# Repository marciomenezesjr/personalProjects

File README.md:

# Personal Projects - Marcio Menezes
This repository has been created with the intention to share some personal projects which I have been developing lately. In time I intend to share projects developed in the past, however it will take some time to clean up and document older projects so they can be shared.

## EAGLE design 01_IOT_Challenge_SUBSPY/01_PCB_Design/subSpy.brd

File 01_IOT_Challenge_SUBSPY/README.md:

# **Internet of Things Challenge**

* Marcio Jose de Menezes

[//]: # (Image References)

[image1]: 06_Images/InternetOfThings.jpg "IoT Challenge Award"

## **1. Introduction: The SubSpy Project**
This project has been developed for the Internet of Things (IoT) contest and has been awarded the first place on the competition. The project has been dubbed SubSpy, since it is a device to capture network packets (spy) in a sub-GHz (sub) wireless sensor network.

 The competition goal was to design a USB wireless adapter to enable handheld devices to connect to an existing sub-GHz underground wireless sensor network used in a project which targets the monitoring of soil moisture in a reforestation project in Cameroon, but could also serve any other underground monitoring application.

Besides the construction of the wireless adapter, a graphical user interface (GUI) was also required, in order to log the sensor's data as well as graphically plot the sensor's readings. The following criteria ([IoT_Project_Evaluation.pdf](08_References/IoT_Project_Evaluation.pdf)) have been used to evaluate the projects:
* Implementation with least number of components
* Low power consumption
* Successful data reception and visualization
* User friendly graphical interface (voted by all students and professors)
* Cost effective solution

The SubSpy project has excelled in each of the evaluating points, being awarded the first place on the challenge.

![alt text][image1]
Image 1: IoT Challenge award

## **2. Content**
Below, the work developed along this project is listed, for further information, refer to the final project report [finalReportIOT.pdf](07_Final_Report/finalReportIOT_lowResolution.pdf)

* Hardware design of the wireless adapter using EAGLE
* Prototype assembly
* Arduino RFM69CW library ported to Texas Instruments MSP430F5529
* Wireless adapter (SubSpy) firmware development in C programming language
* Graphical User Interface developed in cpp using QT framework
* Power consumption profiling benchmarks using EnergyTrace

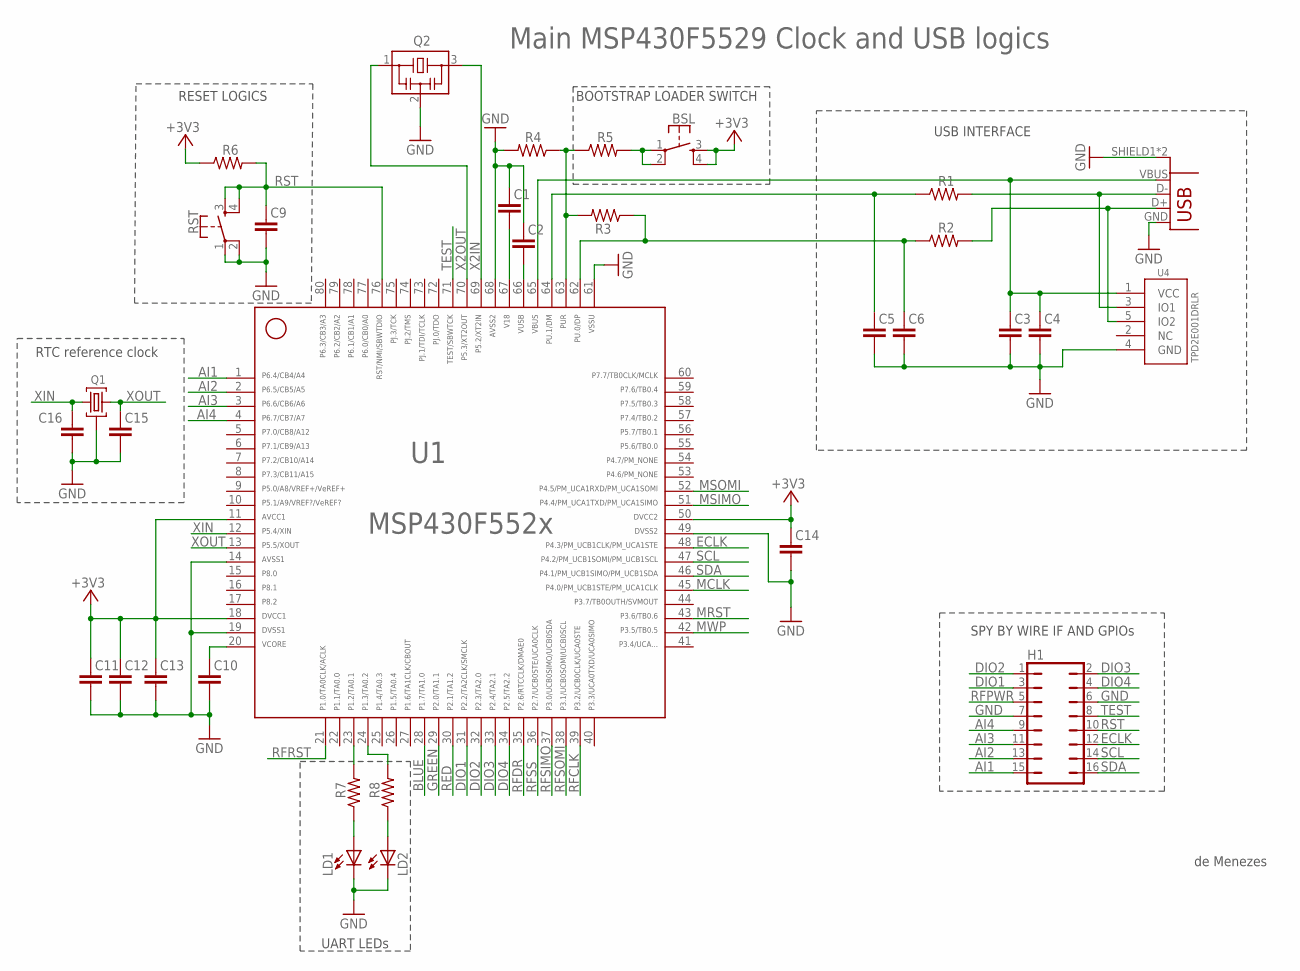
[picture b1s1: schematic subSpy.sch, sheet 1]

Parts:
BSL: DTSM-6
C1, C2: 220nF; C0402
C3: 10uF; C1206
C4, C12, C13, C14: 100nF; C0402
C5, C6: 10pF; C0603
C9: 1nF; C0603
C10: 470nF; C0603
C11: 10uF; C0805
C15, C16: 12pF; C0603
H1: JP8Q
LD1, LD2: LEDCHIP-LED0805; CHIP-LED0805
Q1: 32.768kHz; MS3V-T1R
Q2: CSTCR4M00G15L99; MURATA-FILTER_CSTCR
R1, R2: 27R; R0603
R3: 1.4k; R0603
R4: 1M; R0603
R5: 100R; R0603
R6: 47k; R0603
R7: 470R; R0603
R8: 390R; R0603
RST: DTSM-6
U1: MSP430F5529IPNR; PN80
U4: TPD2E001DRLR; TPD2E001-DRL
USB: USB_SMD; USBCONN

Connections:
+3V3: BSL.3, BSL.4, C11.1, C12.1, C13.1, C14.1, R6.1, U1.11, U1.18, U1.50; also elsewhere on the board
AI1: H1.15, U1.1
AI2: H1.13, U1.2
AI3: H1.11, U1.3
AI4: H1.9, U1.4
BLUE: U1.28; also elsewhere on the board
D+: R2.2, U4.5 (IO2), USB.D+
D-: R1.2, U4.3 (IO1), USB.D-
DIO1: H1.3, U1.31
DIO2: H1.1, U1.32
DIO3: H1.2, U1.33
DIO4: H1.4, U1.34
DM: C5.1, R1.1, U1.64
DP: C6.1, R2.1, R3.1, U1.62
ECLK: H1.12, U1.48
GND: C1.1, C2.1, C3.2, C4.2, C5.2, C6.2, C9.2, C10.2, C11.2, C12.2, C13.2, C14.2, C15.2, C16.2, H1.6, H1.7, LD1.C, LD2.C, Q1.P3 (GND), Q2.2, R4.2, RST.1, RST.2, U1.14, U1.19, U1.49, U1.61, U1.68, U4.4 (GND), USB.GND, USB.SHIELD1 (SHIELD), USB.SHIELD2 (SHIELD); also elsewhere on the board
GREEN: U1.29; also elsewhere on the board
LD1: R7.2, U1.23
LD2: R8.2, U1.24
MCLK: U1.45; also elsewhere on the board
MRST: U1.43; also elsewhere on the board
MSIMO: U1.51; also elsewhere on the board
MSOMI: U1.52; also elsewhere on the board
MWP: U1.42; also elsewhere on the board
unnamed: BSL.1, BSL.2, R5.2
unnamed: C10.1, U1.20
unnamed: LD1.A, R7.1
unnamed: LD2.A, R8.1
PUR: R3.2, R4.1, R5.1, U1.63
RED: U1.30; also elsewhere on the board
RFCLK: U1.39; also elsewhere on the board
RFDR: U1.35; also elsewhere on the board
RFPWR: H1.5; also elsewhere on the board
RFRST: U1.21; also elsewhere on the board
RFSIMO: U1.37; also elsewhere on the board
RFSOMI: U1.38; also elsewhere on the board
RFSS: U1.36; also elsewhere on the board
RST: C9.1, H1.10, R6.2, RST.3, RST.4, U1.76
SCL: H1.14, U1.47
SDA: H1.16, U1.46
TEST: H1.8, U1.71
V18: C1.2, U1.67
VBUS: C3.1, C4.1, U1.65, U4.1 (VCC), USB.VBUS; also elsewhere on the board
VUSB: C2.2, U1.66
X2IN: Q2.3, U1.69
X2OUT: Q2.1, U1.70
XIN: C16.1, Q1.P2 (2), U1.12
XOUT: C15.1, Q1.P1 (1), U1.13

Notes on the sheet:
UART LEDs
SPY BY WIRE IF AND GPIOs
USB INTERFACE
BOOTSTRAP LOADER SWITCH
RESET LOGICS
Main MSP430F5529 Clock and USB logics
RTC reference clock
de Menezes

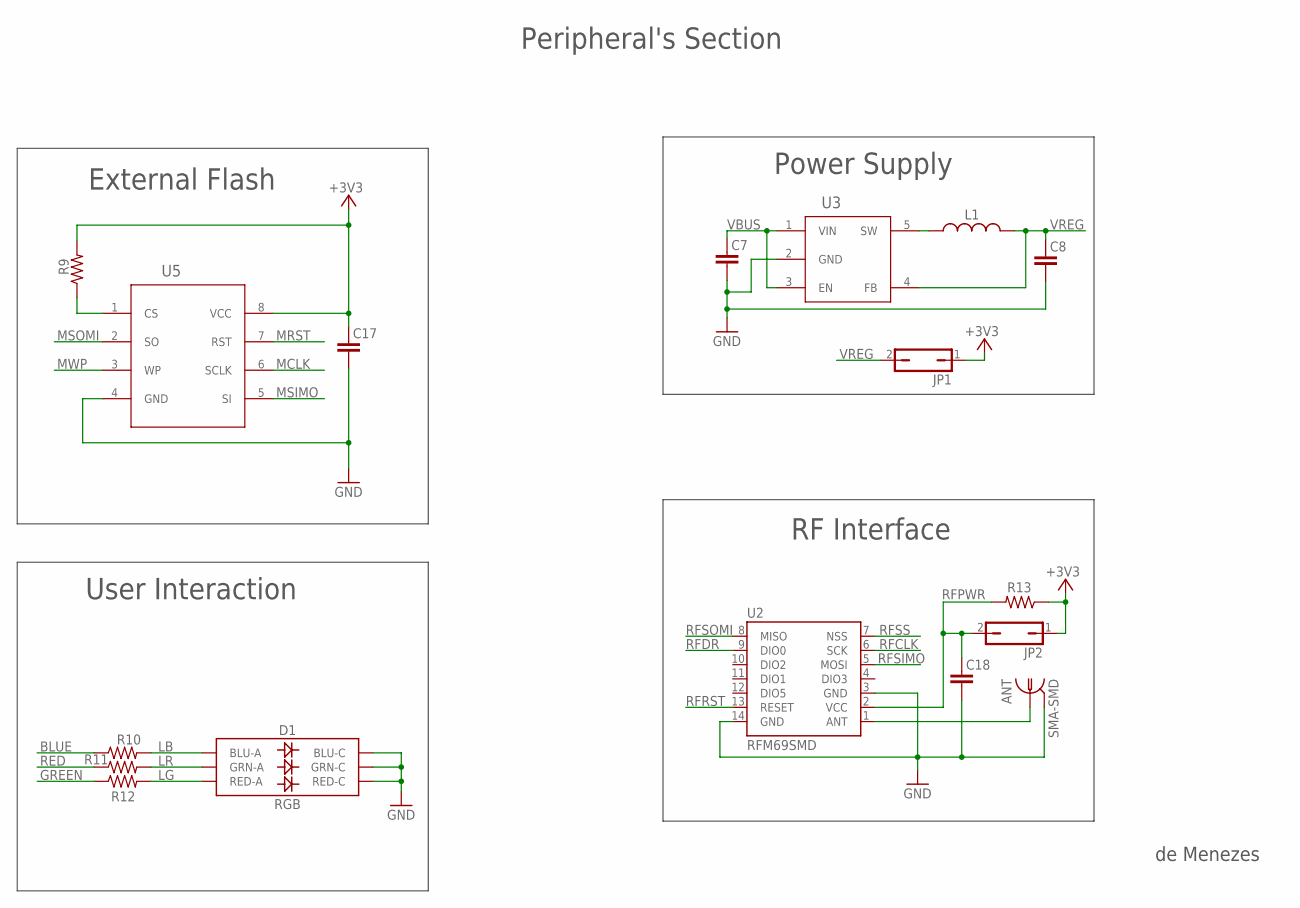
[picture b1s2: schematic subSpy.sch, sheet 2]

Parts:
ANT: SMA-SMD
C7, C8: 10uF; C0805
C17, C18: 100nF; C0402
D1: RGB; PLCC-6-LED
JP1, JP2: JP1Q; JP1
L1: INDUCTOR; L4532P
R9: 2.2k; R0603
R10, R12: ND; R0402
R11: 174R; R0402
R13: 0R; R0603
U2: RFM69SMD; RFM69
U3: Value; DBV0005A_N
U5: Value; PSA0008A_N

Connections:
+3V3: C17.1, JP1.1, JP2.1, R9.2, R13.1, U5.8 (VCC); also elsewhere on the board
ANT: ANT.1, U2.1 (ANT)
BLUE: R10.1; also elsewhere on the board
GND: ANT.2@1 (2), ANT.2@2 (2), ANT.2@3 (2), ANT.2@4 (2), ANT.2@5 (2), ANT.2@6 (2), C7.2, C8.2, C17.2, C18.2, D1.CB (BLU-C), D1.CG (GRN-C), D1.CR (RED-C), U2.3 (GND), U2.14 (GND), U3.2 (GND), U5.4 (GND); also elsewhere on the board
GREEN: R12.1; also elsewhere on the board
LB: D1.AB (BLU-A), R10.2
LG: D1.AR (RED-A), R12.2
LR: D1.AG (GRN-A), R11.2
MCLK: U5.6 (SCLK); also elsewhere on the board
MRST: U5.7 (RST); also elsewhere on the board
MSIMO: U5.5 (SI); also elsewhere on the board
MSOMI: U5.2 (SO); also elsewhere on the board
MSS: R9.1, U5.1 (CS)
MWP: U5.3 (WP); also elsewhere on the board
unnamed: L1.1, U3.5 (SW)
RED: R11.1; also elsewhere on the board
RFCLK: U2.6 (SCK); also elsewhere on the board
RFDR: U2.9 (DIO0); also elsewhere on the board
RFPWR: C18.1, JP2.2, R13.2, U2.2 (VCC); also elsewhere on the board
RFRST: U2.13 (RESET); also elsewhere on the board
RFSIMO: U2.5 (MOSI); also elsewhere on the board
RFSOMI: U2.8 (MISO); also elsewhere on the board
RFSS: U2.7 (NSS); also elsewhere on the board
VBUS: C7.1, U3.1 (VIN), U3.3 (EN); also elsewhere on the board
VREG: C8.1, JP1.2, L1.2, U3.4 (FB)

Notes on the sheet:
External Flash
Power Supply
RF Interface
User Interaction
Peripheral's Section
de Menezes

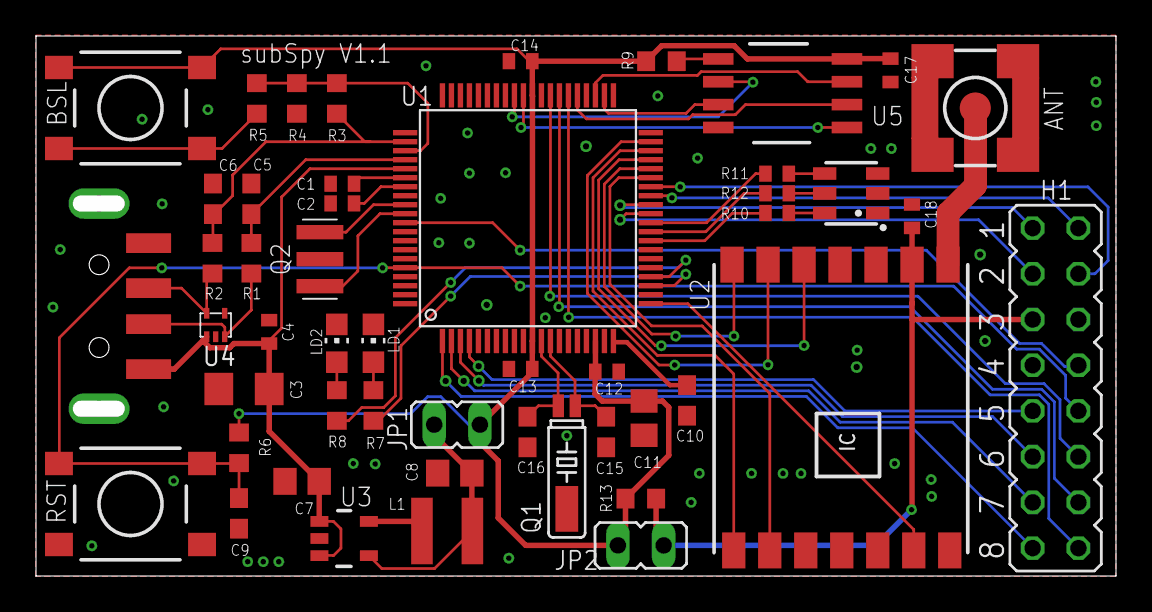
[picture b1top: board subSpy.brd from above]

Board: 2 copper layers, 60.0 x 30.0 mm, 49 parts (0 on the bottom side), 55 nets.

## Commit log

2017-07-29 Initial commit: personal projects moved to version control.
2017-07-30 Included folium maps to python project Taxi Data Analysis
2018-05-07 Included C projects to version control.

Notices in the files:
parts and their libraries:
sparkfun: Licensing: Creative Commons ShareAlike 4.0 International - https://creativecommons.org/licenses/by-sa/4.0
